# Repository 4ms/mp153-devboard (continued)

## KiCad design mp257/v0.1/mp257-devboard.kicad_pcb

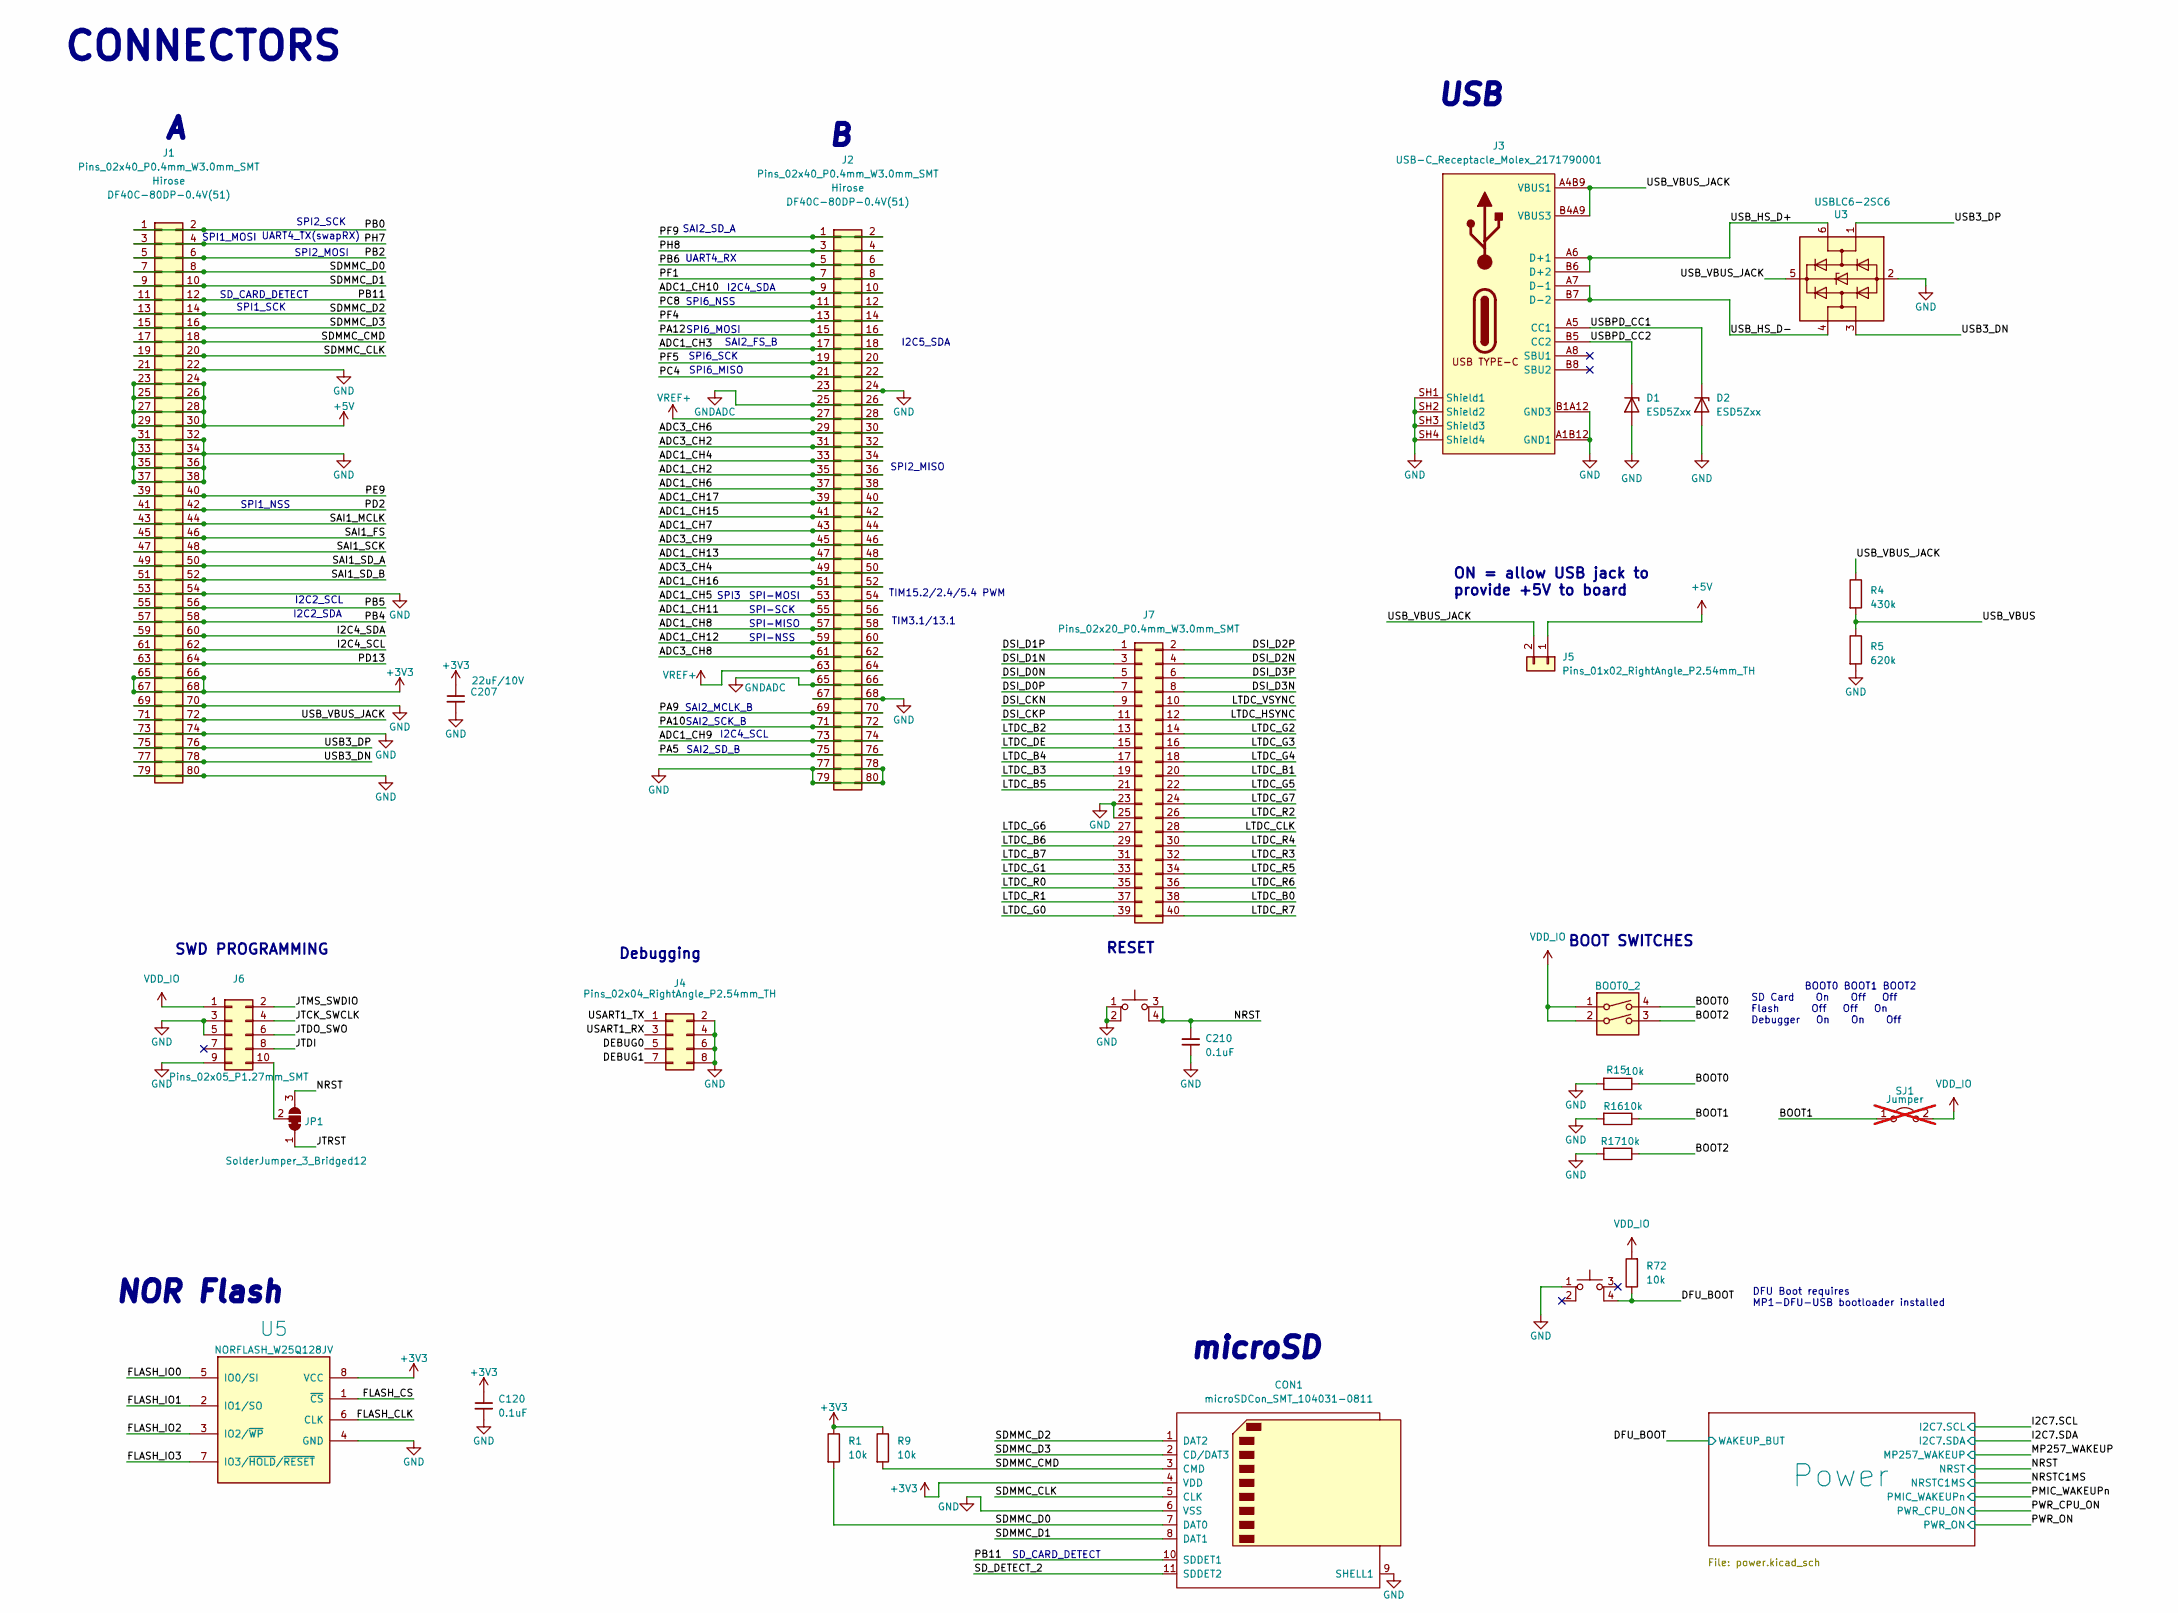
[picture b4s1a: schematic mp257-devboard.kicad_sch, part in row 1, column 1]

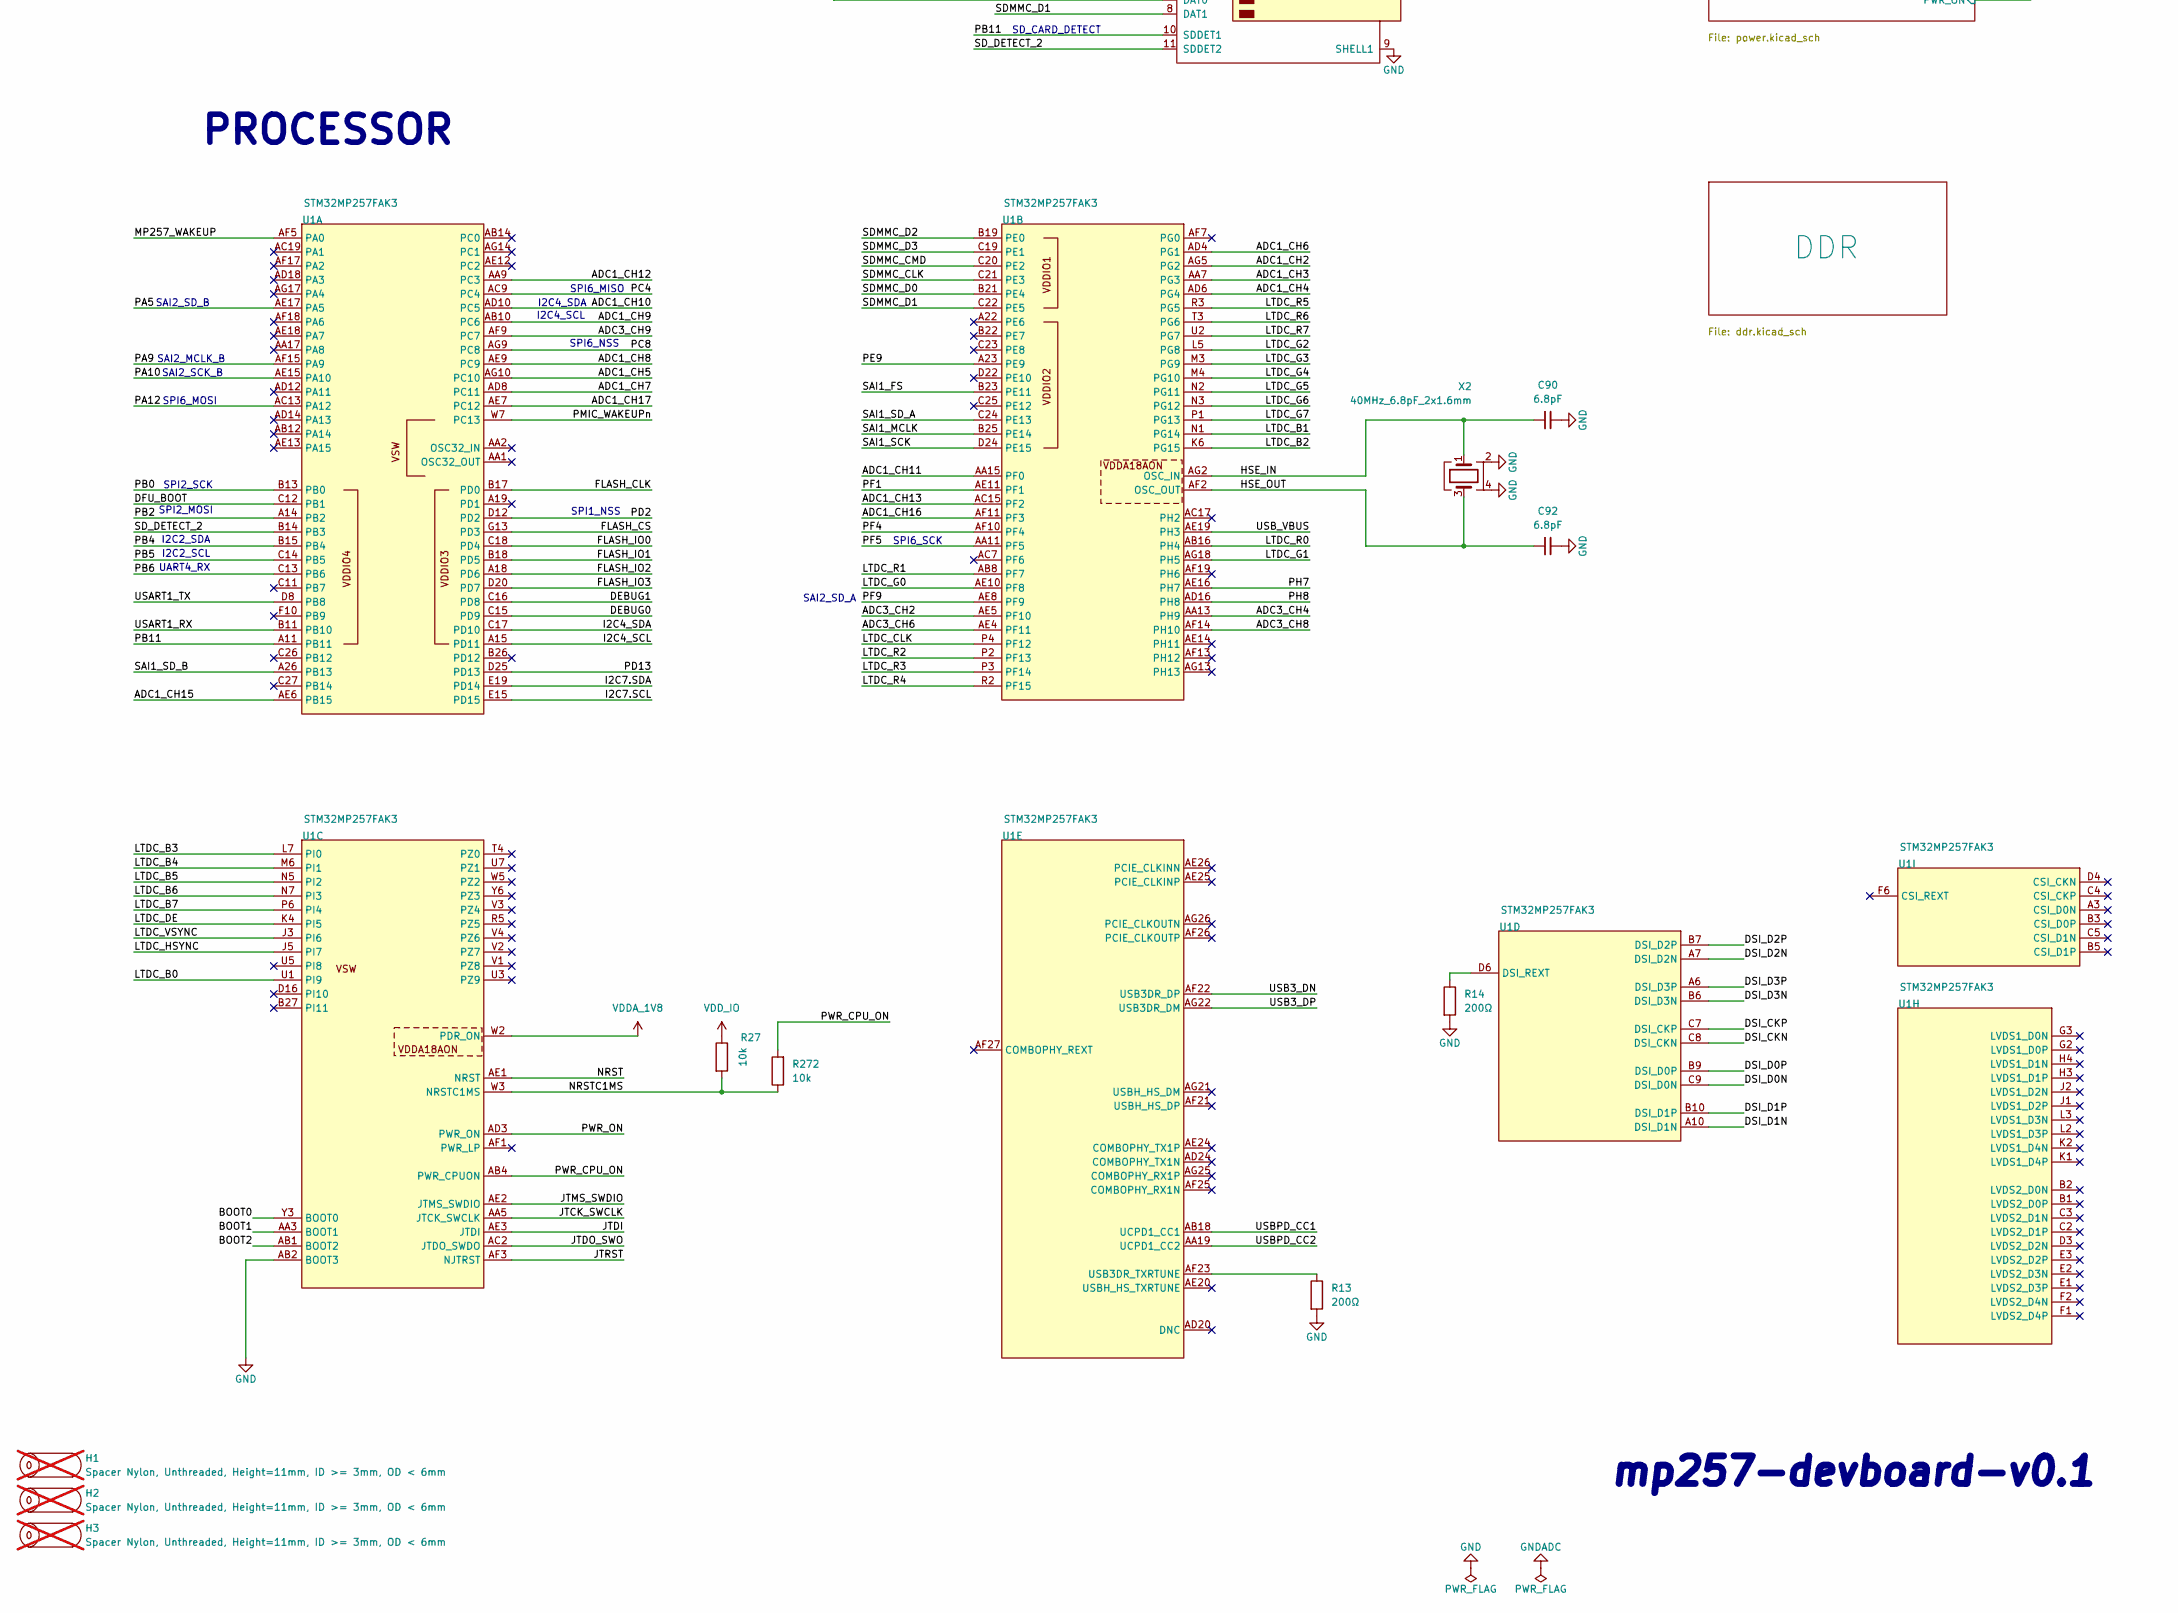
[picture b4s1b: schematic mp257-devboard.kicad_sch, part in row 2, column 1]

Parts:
BOOT0_2: SW_DIP_x02_CTS_219-2MST; SW_DIP_SPSTx02_CTS_219-2MSTR; Part Number 219-2MST; JLCPCB ID C2961978
C90, C92: 6.8pF_0402_25V; C_0402; Part Number CC0402CRNPO9BN6R8; JLCPCB ID C1576
C120, C210: 100nF_0402_16V; C_0402; Part Number GCM155R71C104KA55D; JLCPCB ID C1525
C207: 22uF_0805_10V; C_0805; Part Number LMK212BBJ226MG-T; JLCPCB ID C45783
CON1: microSDCon_SMT_104031-0811; CardSlot_MicroSD_Molex_104031-0811; Part Number 104031-0811; JLCPCB ID C585350
D1, D2: ESD5Zxx; D_SOD-523; Part Number ESD7351XV2T1G
H1, H2, H3: Spacer Nylon, Unthreaded, Height=11mm, ID >= 3mm,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; MountingHole_Generic_3mm; Part Number 93657A504; not fitted
J1, J2: Pins_02x40_P0.4mm_W3.0mm_SMT; Connector-80pin-P0.4mm-W3.0mm; Part Number DF40C-80DP-0.4V(51); JLCPCB ID C294544
J3: USB-C_Receptacle_Molex_2171790001; USB_C_Receptacle_Molex_2171790001; Part Number 217179-0001; JLCPCB ID C2894899
J4: Pins_02x04_RightAngle_P2.54mm_TH; Pins_2x04_P2.54mm_Horizontal_CroppedSilk; Part Number TSW-104-08-T-D-RA
J5: Pins_01x02_RightAngle_P2.54mm_TH; Pins_1x02_2.54mm_TH; Part Number TSW-102-08-T-S-RA
J6: Pins_02x05_P1.27mm_SMT; Pins_2x05_1.27mm_SMD; Part Number FTSH-105-01-F-DV; JLCPCB ID C598540
J7: Pins_02x20_P0.4mm_W3.0mm_SMT; Connector-40pin-P0.4mm-W3.0mm; Part Number DF40C-40DP-0.4V(51); JLCPCB ID C424643
JP1: SolderJumper_3_Bridged12; JUMPER_SMD_1x3_tiny_shorted12
R1, R9, R15, R16, R17, R27, R72, R272: 10k_0402; R_0402; Part Number RC0402FR-0710KL; JLCPCB ID C60490
R4: 430k_0402; R_0402; Part Number RC0402FR-07430KL; JLCPCB ID C163463
R5: 620k_0402; R_0402; Part Number RC0402FR-07620KL; JLCPCB ID C137952
R13, R14: 200Ω_0402; R_0402; Part Number RC0402FR-07200RL; JLCPCB ID C114764
S2, S3: SW_Push_PTS526 SM15 SMTR2 LFS; Button_Tact_PTS526; Part Number PTS526 SM15 SMTR2 LFS; JLCPCB ID C2689521
SJ1: Jumper; JUMPER_SMD_1x2; not fitted
U1: STM32MP257FAK3; TFBGA-424_14x14mm_P0.5_STM_AK; Part Number STM32MP257FAK3
U3: USBLC6-2SC6; SOT-23-6; Part Number USBLC6-2SC6; JLCPCB ID C2827654
U5: NORFLASH_W25Q128JV; SOIC-8_5.28x4.9mm_Pitch1.27mm; Part Number W25Q128JVSIQ; JLCPCB ID C113767
X2: 40MHz_6.8pF_2x1.6mm; Crystal_2.0x1.6mm_4pin; Part Number XRCGB40M000F0G00R0; JLCPCB ID C50396645

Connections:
+3V3: C120.1, C207.1, CON1.4 (VDD), J1.65, J1.66, J1.67, J1.68, R1.1, R9.1, U5.8 (VCC); also elsewhere on the board
+5V: J1.23, J1.24, J1.25, J1.26, J1.27, J1.28, J1.29, J1.30, J5.1; also elsewhere on the board
/ADC1_CH2: J2.35, J2.36, U1.AG5 (PG2)
/ADC1_CH3: J2.17, J2.18, U1.AA7 (PG3)
/ADC1_CH4: J2.33, J2.34, U1.AD6 (PG4)
/ADC1_CH5: J2.53, J2.54, U1.AG10 (PC10)
/ADC1_CH6: J2.37, J2.38, U1.AD4 (PG1)
/ADC1_CH7: J2.43, J2.44, U1.AD8 (PC11)
/ADC1_CH8: J2.57, J2.58, U1.AE9 (PC9)
/ADC1_CH9: J2.73, J2.74, U1.AB10 (PC6)
/ADC1_CH10: J2.9, J2.10, U1.AD10 (PC5)
/ADC1_CH11: J2.55, J2.56, U1.AA15 (PF0)
/ADC1_CH12: J2.59, J2.60, U1.AA9 (PC3)
/ADC1_CH13: J2.47, J2.48, U1.AC15 (PF2)
/ADC1_CH15: J2.41, J2.42, U1.AE6 (PB15)
/ADC1_CH16: J2.51, J2.52, U1.AF11 (PF3)
/ADC1_CH17: J2.39, J2.40, U1.AE7 (PC12)
/ADC3_CH2: J2.31, J2.32, U1.AE5 (PF10)
/ADC3_CH4: J2.49, J2.50, U1.AA13 (PH9)
/ADC3_CH6: J2.29, J2.30, U1.AE4 (PF11)
/ADC3_CH8: J2.61, J2.62, U1.AF14 (PH10)
/ADC3_CH9: J2.45, J2.46, U1.AF9 (PC7)
/BOOT0: BOOT0_2.4, R15.1, U1.Y3 (BOOT0)
/BOOT1: R16.1, SJ1.1 (A), U1.AA3 (BOOT1)
/BOOT2: BOOT0_2.3, R17.1, U1.AB1 (BOOT2)
/DEBUG0: J4.5, U1.C15 (PD9)
/DEBUG1: J4.7, U1.C16 (PD8)
/DFU_BOOT: R72.1, S3.4, U1.C12 (PB1); also elsewhere on the board
/DSI_CKN: J7.9, U1.C8 (DSI_CKN)
/DSI_CKP: J7.11, U1.C7 (DSI_CKP)
/DSI_D0N: J7.5, U1.C9 (DSI_D0N)
/DSI_D0P: J7.7, U1.B9 (DSI_D0P)
/DSI_D1N: J7.3, U1.A10 (DSI_D1N)
/DSI_D1P: J7.1, U1.B10 (DSI_D1P)
/DSI_D2N: J7.4, U1.A7 (DSI_D2N)
/DSI_D2P: J7.2, U1.B7 (DSI_D2P)
/DSI_D3N: J7.8, U1.B6 (DSI_D3N)
/DSI_D3P: J7.6, U1.A6 (DSI_D3P)
/FLASH_CLK: U1.B17 (PD0), U5.6 (CLK)
/FLASH_CS: U1.G13 (PD3), U5.1 (~CS)
/FLASH_IO0: U1.C18 (PD4), U5.5 (IO0/SI)
/FLASH_IO1: U1.B18 (PD5), U5.2 (IO1/SO)
/FLASH_IO2: U1.A18 (PD6), U5.3 (IO2/~WP)
/FLASH_IO3: U1.D20 (PD7), U5.7 (IO3/~HOLD/~RESET)
/HSE_IN: C90.1, U1.AG2 (OSC_IN), X2.1
/HSE_OUT: C92.1, U1.AF2 (OSC_OUT), X2.3
/I2C4_SCL: J1.61, J1.62, U1.A15 (PD11)
/I2C4_SDA: J1.59, J1.60, U1.C17 (PD10)
/I2C7.SCL: U1.E15 (PD15); also elsewhere on the board
/I2C7.SDA: U1.E19 (PD14); also elsewhere on the board
/JTCK_SWCLK: J6.4, U1.AA5 (JTCK_SWCLK)
/JTDI: J6.8, U1.AE3 (JTDI)
/JTDO_SWO: J6.6, U1.AC2 (JTDO_SWDO)
/JTMS_SWDIO: J6.2, U1.AE2 (JTMS_SWDIO)
/JTRST: JP1.1 (A), U1.AF3 (NJTRST)
/LTDC_B0: J7.38, U1.U1 (PI9)
/LTDC_B1: J7.20, U1.N1 (PG14)
/LTDC_B2: J7.13, U1.K6 (PG15)
/LTDC_B3: J7.19, U1.L7 (PI0)
/LTDC_B4: J7.17, U1.M6 (PI1)
/LTDC_B5: J7.21, U1.N5 (PI2)
/LTDC_B6: J7.29, U1.N7 (PI3)
/LTDC_B7: J7.31, U1.P6 (PI4)
/LTDC_CLK: J7.28, U1.P4 (PF12)
/LTDC_DE: J7.15, U1.K4 (PI5)
/LTDC_G0: J7.39, U1.AE10 (PF8)
/LTDC_G1: J7.33, U1.AG18 (PH5)
/LTDC_G2: J7.14, U1.L5 (PG8)
/LTDC_G3: J7.16, U1.M3 (PG9)
/LTDC_G4: J7.18, U1.M4 (PG10)
/LTDC_G5: J7.22, U1.N2 (PG11)
/LTDC_G6: J7.27, U1.N3 (PG12)
/LTDC_G7: J7.24, U1.P1 (PG13)
/LTDC_HSYNC: J7.12, U1.J5 (PI7)
/LTDC_R0: J7.35, U1.AB16 (PH4)
/LTDC_R1: J7.37, U1.AB8 (PF7)
/LTDC_R2: J7.26, U1.P2 (PF13)
/LTDC_R3: J7.32, U1.P3 (PF14)
/LTDC_R4: J7.30, U1.R2 (PF15)
/LTDC_R5: J7.34, U1.R3 (PG5)
/LTDC_R6: J7.36, U1.T3 (PG6)
/LTDC_R7: J7.40, U1.U2 (PG7)
/LTDC_VSYNC: J7.10, U1.J3 (PI6)
/MP257_WAKEUP: U1.AF5 (PA0); also elsewhere on the board
/NRST: C210.2, JP1.3 (B), S2.3, S2.4, U1.AE1 (NRST); also elsewhere on the board
/NRSTC1MS: R27.2, R272.1, U1.W3 (NRSTC1MS); also elsewhere on the board
/PA5: J2.75, J2.76, U1.AE17 (PA5)
/PA9: J2.69, J2.70, U1.AF15 (PA9)
/PA10: J2.71, J2.72, U1.AE15 (PA10)
/PA12: J2.15, J2.16, U1.AC13 (PA12)
/PB0: J1.1, J1.2, U1.B13 (PB0)
/PB2: J1.5, J1.6, U1.A14 (PB2)
/PB4: J1.57, J1.58, U1.B15 (PB4)
/PB5: J1.55, J1.56, U1.C14 (PB5)
/PB6: J2.5, J2.6, U1.C13 (PB6)
/PB11: CON1.10 (SDDET1), J1.11, J1.12, U1.A11 (PB11)
/PC4: J2.21, J2.22, U1.AC9 (PC4)
/PC8: J2.11, J2.12, U1.AG9 (PC8)
/PD2: J1.41, J1.42, U1.D12 (PD2)
/PD13: J1.63, J1.64, U1.D25 (PD13)
/PE9: J1.39, J1.40, U1.A23 (PE9)
/PF1: J2.7, J2.8, U1.AE11 (PF1)
/PF4: J2.13, J2.14, U1.AF10 (PF4)
/PF5: J2.19, J2.20, U1.AA11 (PF5)
/PF9: J2.1, J2.2, U1.AE8 (PF9)
/PH7: J1.3, J1.4, U1.AE16 (PH7)
/PH8: J2.3, J2.4, U1.AD16 (PH8)
/PMIC_WAKEUPn: U1.W7 (PC13); also elsewhere on the board
/PWR_CPU_ON: R272.2, U1.AB4 (PWR_CPUON); also elsewhere on the board
/PWR_ON: U1.AD3 (PWR_ON); also elsewhere on the board
/SAI1_FS: J1.45, J1.46, U1.B23 (PE11)
/SAI1_MCLK: J1.43, J1.44, U1.B25 (PE14)
/SAI1_SCK: J1.47, J1.48, U1.D24 (PE15)
/SAI1_SD_A: J1.49, J1.50, U1.C24 (PE13)
/SAI1_SD_B: J1.51, J1.52, U1.A26 (PB13)
/SDMMC_CLK: CON1.5 (CLK), J1.19, J1.20, U1.C21 (PE3)
/SDMMC_CMD: CON1.3 (CMD), J1.17, J1.18, R9.2, U1.C20 (PE2)
/SDMMC_D0: CON1.7 (DAT0), J1.7, J1.8, R1.2, U1.B21 (PE4)
/SDMMC_D1: CON1.8 (DAT1), J1.9, J1.10, U1.C22 (PE5)
/SDMMC_D2: CON1.1 (DAT2), J1.13, J1.14, U1.B19 (PE0)
/SDMMC_D3: CON1.2 (CD/DAT3), J1.15, J1.16, U1.C19 (PE1)
/SD_DETECT_2: CON1.11 (SDDET2), U1.B14 (PB3)
/USART1_RX: J4.3, U1.B11 (PB10)
/USART1_TX: J4.1, U1.D8 (PB8)
/USB3_DN: J1.77, J1.78, U1.AF22 (USB3DR_DP), U3.3 (I/O2)
/USB3_DP: J1.75, J1.76, U1.AG22 (USB3DR_DM), U3.1 (I/O1)
/USBPD_CC1: D2.1 (K), J3.A5 (CC1), U1.AB18 (UCPD1_CC1)
/USBPD_CC2: D1.1 (K), J3.B5 (CC2), U1.AA19 (UCPD1_CC2)
/USB_HS_D+: J3.A6 (D+1), J3.B6 (D+2), U3.6 (I/O1)
/USB_HS_D-: J3.A7 (D-1), J3.B7 (D-2), U3.4 (I/O2)
/USB_VBUS: R4.2, R5.1, U1.AE19 (PH3)
/USB_VBUS_JACK: J1.71, J1.72, J3.A4B9 (VBUS1), J3.B4A9 (VBUS3), J5.2, R4.1, U3.5 (VBUS)
GND: C90.2, C92.2, C120.2, C207.2, C210.1, CON1.6 (VSS), CON1.9 (SHELL1), D1.2 (A), D2.2 (A), J1.21, J1.22, J1.31, J1.32, J1.33, J1.34, J1.35, J1.36, J1.37, J1.38, J1.53, J1.54, J1.69, J1.70, J1.73, J1.74, J1.79, J1.80, J2.23, J2.24, J2.67, J2.68, J2.77, J2.78, J2.79, J2.80, J3.A1B12 (GND1), J3.B1A12 (GND3), J3.SH1 (Shield1), J3.SH2 (Shield2), J3.SH3 (Shield3), J3.SH4 (Shield4), J4.2, J4.4, J4.6, J4.8, J6.3, J6.5, J6.9, J7.23, J7.25, R5.2, R13.2, R14.2, R15.2, R16.2, R17.2, S2.1, S2.2, S3.1, U1.AB2 (BOOT3), U3.2 (GND), U5.4 (GND), X2.2, X2.4; also elsewhere on the board
GNDADC: J2.25, J2.26, J2.65, J2.66; also elsewhere on the board
unnamed: J6.10, JP1.2 (C)
unnamed: R14.1, U1.D6 (DSI_REXT)
unnamed: R13.1, U1.AF23 (USB3DR_TXRTUNE)
VDDA_1V8: U1.W2 (PDR_ON); also elsewhere on the board
VDD_IO: BOOT0_2.1, BOOT0_2.2, J6.1, R27.1, R72.2, SJ1.2 (B); also elsewhere on the board
VREF+: J2.27, J2.28, J2.63, J2.64; also elsewhere on the board

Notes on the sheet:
SPI1_MOSI
DFU Boot requires MP1-DFU-USB bootloader installed
microSD
I2C2_SDA
UART4_RX
I2C4_SCL
SPI6_NSS
SD_CARD_DETECT
SPI6_SCK
I2C4_SDA
SAI2_SD_A
I2C5_SDA
SAI2_MCLK_B
BOOT SWITCHES
mp257-devboard-v0.1
SPI-MOSI
SPI2_MOSI
SWD PROGRAMMING
I2C2_SCL
CONNECTORS
SPI6_MISO
SPI2_SCK
SPI1_NSS
SAI2_SD_B
SAI2_SCK_B
SPI1_SCK
SPI6_MOSI
USB
SPI-MISO
SAI2_FS_B
PROCESSOR
TIM15.2/2.4/5.4 PWM
UART4_TX(swapRX)
SPI-SCK
RESET
SPI-NSS
BOOT0 BOOT1 BOOT2 SD Card On Off Off Flash Off Off On Debugger On On Off
ON = allow USB jack to provide +5V to board
SPI3
SPI2_MISO
